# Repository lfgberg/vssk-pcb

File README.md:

# vssk-pcb
PCB for dudeship's VSSK keyboard

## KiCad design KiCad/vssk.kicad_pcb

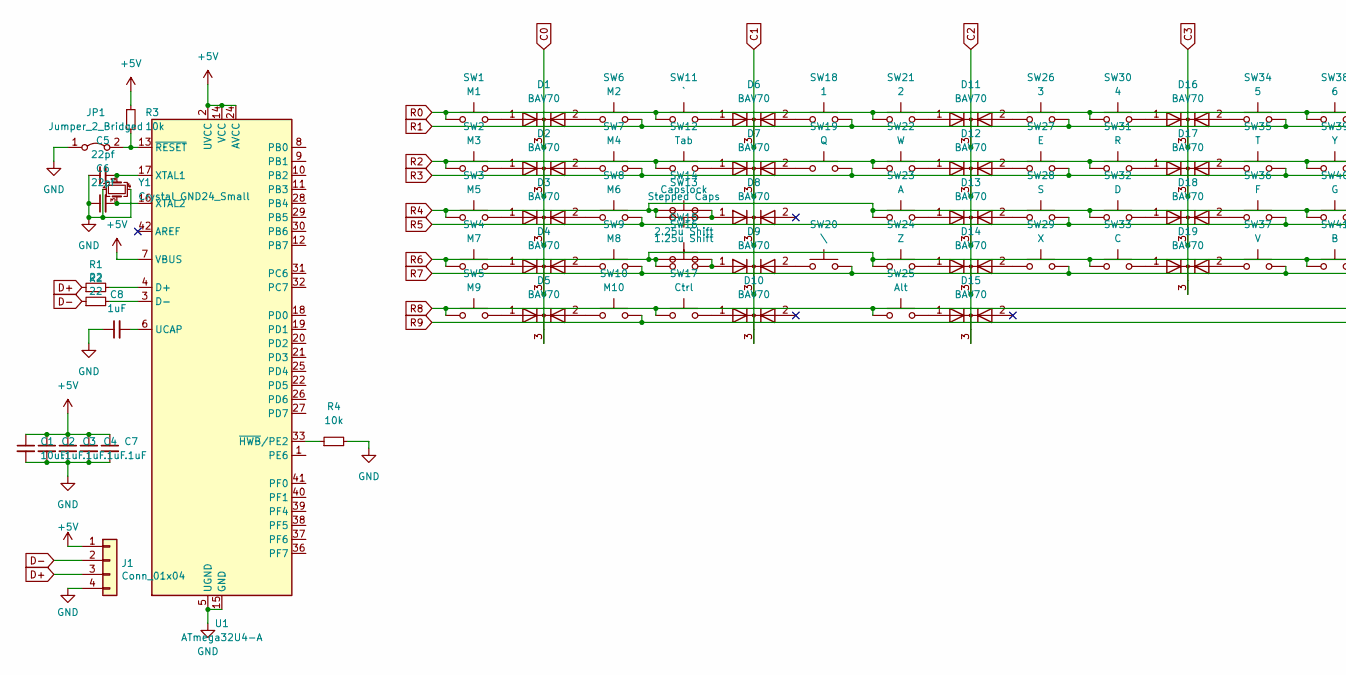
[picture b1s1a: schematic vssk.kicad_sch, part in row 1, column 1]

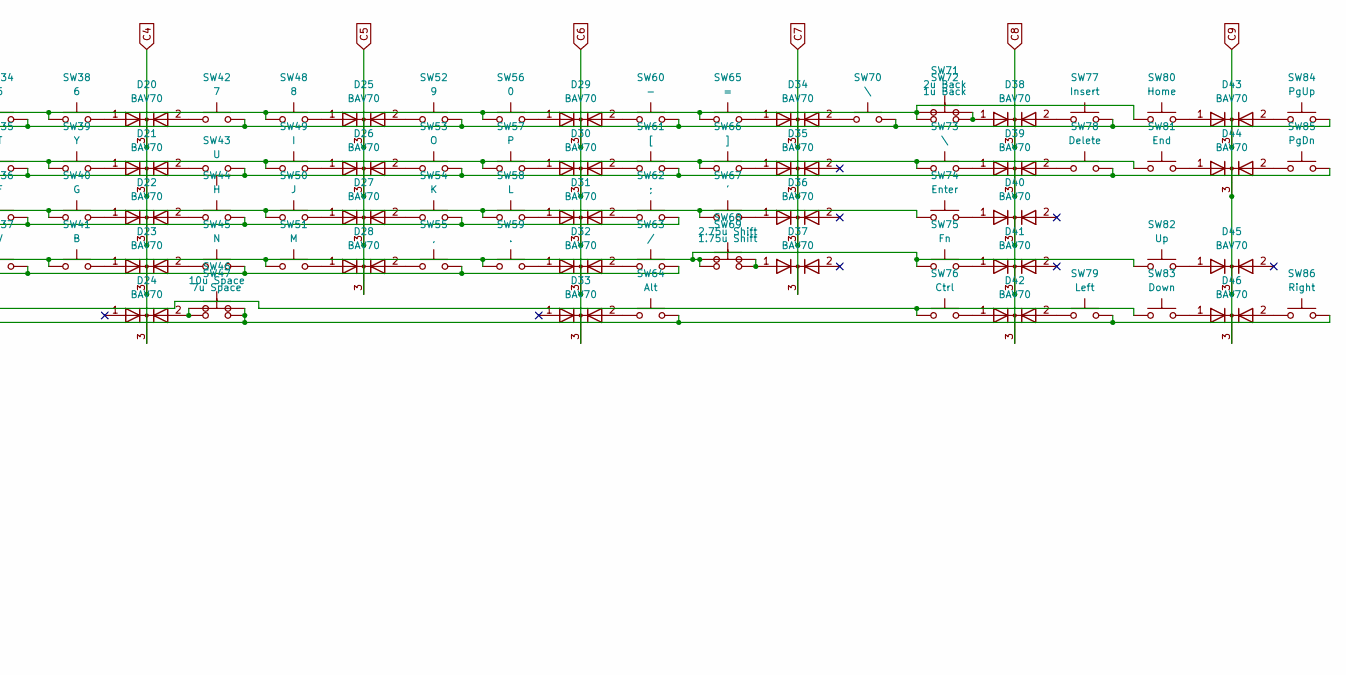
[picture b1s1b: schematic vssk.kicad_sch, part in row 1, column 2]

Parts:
C1: 10uF; C_0805_2012Metric
C2, C3, C4, C7: .1uF; C_0805_2012Metric
C5, C6: 22pf; C_0805_2012Metric
C8: 1uF; C_0805_2012Metric
D1, D2, D3, D4, D5, D6, D7, D8, D9, D10, D11, D12, D13, D14, D15, D16, D17, D18, D19, D20, D21, D22, D23, D24, D25, D26, D27, D28, D29, D30, D31, D32, D33, D34, D35, D36, D37, D38, D39, D40, D41, D42, D43, D44, D45, D46: BAV70; SOT-23
J1: Conn_01x04; JST-SR-4
JP1: Jumper_2_Bridged; ResetJumper
R1, R2: 22; R_0805_2012Metric
R3, R4: 10k; R_0805_2012Metric
SW1: M1; MX-1U-NoLED
SW2: M3; MX-1U-NoLED
SW3: M5; MX-1U-NoLED
SW4: M7; MX-1U-NoLED
SW5: M9; MX-1U-NoLED
SW6: M2; MX-1U-NoLED
SW7: M4; MX-1U-NoLED
SW8: M6; MX-1U-NoLED
SW9: M8; MX-1U-NoLED
SW10: M10; MX-1U-NoLED
SW11: `; MX-1U-NoLED
SW12: Tab; MX-1.5U-NoLED
SW13: Stepped Caps; MX-1.25U-NoLED
SW14: Capslock; MX-1.75U-NoLED
SW15: 2.25u Shift; MX-2.25U-NoLED
SW16: 1.25u Shift; MX-1.25U-NoLED
SW17, SW76: Ctrl; MX-1.5U-NoLED
SW18: 1; MX-1U-NoLED
SW19: Q; MX-1U-NoLED
SW20, SW70: \; MX-1U-NoLED
SW21: 2; MX-1U-NoLED
SW22: W; MX-1U-NoLED
SW23: A; MX-1U-NoLED
SW24: Z; MX-1U-NoLED
SW25, SW64: Alt; MX-1.5U-NoLED
SW26: 3; MX-1U-NoLED
SW27: E; MX-1U-NoLED
SW28: S; MX-1U-NoLED
SW29: X; MX-1U-NoLED
SW30: 4; MX-1U-NoLED
SW31: R; MX-1U-NoLED
SW32: D; MX-1U-NoLED
SW33: C; MX-1U-NoLED
SW34: 5; MX-1U-NoLED
SW35: T; MX-1U-NoLED
SW36: F; MX-1U-NoLED
SW37: V; MX-1U-NoLED
SW38: 6; MX-1U-NoLED
SW39: Y; MX-1U-NoLED
SW40: G; MX-1U-NoLED
SW41: B; MX-1U-NoLED
SW42: 7; MX-1U-NoLED
SW43: U; MX-1U-NoLED
SW44: H; MX-1U-NoLED
SW45: N; MX-1U-NoLED
SW46: 10u Space; MX-8U-ReversedStabilizers-NoLED
SW47: 7u Space; MX-7U-ReversedStabilizers-NoLED
SW48: 8; MX-1U-NoLED
SW49: I; MX-1U-NoLED
SW50: J; MX-1U-NoLED
SW51: M; MX-1U-NoLED
SW52: 9; MX-1U-NoLED
SW53: O; MX-1U-NoLED
SW54: K; MX-1U-NoLED
SW55: ,; MX-1U-NoLED
SW56: 0; MX-1U-NoLED
SW57: P; MX-1U-NoLED
SW58: L; MX-1U-NoLED
SW59: .; MX-1U-NoLED
SW60: -; MX-1U-NoLED
SW61: [; MX-1U-NoLED
SW62: ;; MX-1U-NoLED
SW63: /; MX-1U-NoLED
SW65: =; MX-1U-NoLED
SW66: ]; MX-1U-NoLED
SW67: '; MX-1U-NoLED
SW68: 2.75u Shift; MX-2.75U-NoLED
SW69: 1.75u Shift; MX-1.75U-NoLED
SW71: 2u Back; MX-2U-NoLED
SW72: 1u Back; MX-1U-NoLED
SW73: \; MX-1.5U-NoLED
SW74: Enter; MX-2.25U-NoLED
SW75: Fn; MX-1U-NoLED
SW77: Insert; MX-1U-NoLED
SW78: Delete; MX-1U-NoLED
SW79: Left; MX-1U-NoLED
SW80: Home; MX-1U-NoLED
SW81: End; MX-1U-NoLED
SW82: Up; MX-1U-NoLED
SW83: Down; MX-1U-NoLED
SW84: PgUp; MX-1U-NoLED
SW85: PgDn; MX-1U-NoLED
SW86: Right; MX-1U-NoLED
U1: ATmega32U4-A; QFN_TQFP-44_Combined
Y1: Crystal_GND24_Small; Crystal_SMD_3225-4Pin_3.2x2.5mm_HandSoldering

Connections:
+5V: C1.1, C2.1, C3.1, C4.1, C7.1, J1.1, R3.1, U1.2 (UVCC), U1.7 (VBUS), U1.14 (VCC), U1.24 (AVCC), U1.34 (VCC), U1.44 (AVCC)
C0: D1.3 (K), D2.3 (K), D3.3 (K), D4.3 (K), D5.3 (K)
C1: D6.3 (K), D7.3 (K), D8.3 (K), D9.3 (K), D10.3 (K)
C2: D11.3 (K), D12.3 (K), D13.3 (K), D14.3 (K), D15.3 (K)
C3: D16.3 (K), D17.3 (K), D18.3 (K), D19.3 (K)
C4: D20.3 (K), D21.3 (K), D22.3 (K), D23.3 (K), D24.3 (K)
C5: D25.3 (K), D26.3 (K), D27.3 (K), D28.3 (K)
C6: D29.3 (K), D30.3 (K), D31.3 (K), D32.3 (K), D33.3 (K)
C7: D34.3 (K), D35.3 (K), D36.3 (K), D37.3 (K)
C8: D38.3 (K), D39.3 (K), D40.3 (K), D41.3 (K), D42.3 (K)
C9: D43.3 (K), D44.3 (K), D45.3 (K), D46.3 (K)
D+: J1.3, R1.1
D-: J1.2, R2.1
GND: C1.2, C2.2, C3.2, C4.2, C5.1, C6.1, C7.2, C8.1, J1.4, JP1.1 (A), R4.2, U1.5 (UGND), U1.15 (GND), U1.23 (GND), U1.35 (GND), U1.43 (GND), Y1.2, Y1.4
unnamed: C5.2, U1.17 (XTAL1), Y1.1
unnamed: C6.2, U1.16 (XTAL2), Y1.3
unnamed: C8.2, U1.6 (UCAP)
unnamed: D1.1 (A), SW1.2
unnamed: D1.2 (A), SW6.1
unnamed: D2.1 (A), SW2.2
unnamed: D2.2 (A), SW7.1
unnamed: D3.1 (A), SW3.2
unnamed: D3.2 (A), SW8.1
unnamed: D4.1 (A), SW4.2
unnamed: D4.2 (A), SW9.1
unnamed: D5.1 (A), SW5.2
unnamed: D5.2 (A), SW10.1
unnamed: D6.1 (A), SW11.2
unnamed: D6.2 (A), SW18.1
unnamed: D7.1 (A), SW12.2
unnamed: D7.2 (A), SW19.1
unnamed: D8.1 (A), SW13.1, SW14.2
unnamed: D9.1 (A), SW15.2, SW16.2
unnamed: D9.2 (A), SW20.1
unnamed: D10.1 (A), SW17.2
unnamed: D11.1 (A), SW21.2
unnamed: D11.2 (A), SW26.1
unnamed: D12.1 (A), SW22.2
unnamed: D12.2 (A), SW27.1
unnamed: D13.1 (A), SW23.2
unnamed: D13.2 (A), SW28.1
unnamed: D14.1 (A), SW24.2
unnamed: D14.2 (A), SW29.1
unnamed: D15.1 (A), SW25.2
unnamed: D16.1 (A), SW30.2
unnamed: D16.2 (A), SW34.1
unnamed: D17.1 (A), SW31.2
unnamed: D17.2 (A), SW35.1
unnamed: D18.1 (A), SW32.2
unnamed: D18.2 (A), SW36.1
unnamed: D19.1 (A), SW33.2
unnamed: D19.2 (A), SW37.1
unnamed: D20.1 (A), SW38.2
unnamed: D20.2 (A), SW42.1
unnamed: D21.1 (A), SW39.2
unnamed: D21.2 (A), SW43.1
unnamed: D22.1 (A), SW40.2
unnamed: D22.2 (A), SW44.1
unnamed: D23.1 (A), SW41.2
unnamed: D23.2 (A), SW45.1
unnamed: D24.2 (A), SW46.1, SW47.1
unnamed: D25.1 (A), SW48.2
unnamed: D25.2 (A), SW52.1
unnamed: D26.1 (A), SW49.2
unnamed: D26.2 (A), SW53.1
unnamed: D27.1 (A), SW50.2
unnamed: D27.2 (A), SW54.1
unnamed: D28.1 (A), SW51.2
unnamed: D28.2 (A), SW55.1
unnamed: D29.1 (A), SW56.2
unnamed: D29.2 (A), SW60.1
unnamed: D30.1 (A), SW57.2
unnamed: D30.2 (A), SW61.1
unnamed: D31.1 (A), SW58.2
unnamed: D31.2 (A), SW62.1
unnamed: D32.1 (A), SW59.2
unnamed: D32.2 (A), SW63.1
unnamed: D33.2 (A), SW64.1
unnamed: D34.1 (A), SW65.2
unnamed: D34.2 (A), SW70.1
unnamed: D35.1 (A), SW66.2
unnamed: D36.1 (A), SW67.2
unnamed: D37.1 (A), SW68.2, SW69.2
unnamed: D38.1 (A), SW71.2, SW72.2
unnamed: D38.2 (A), SW77.1
unnamed: D39.1 (A), SW73.2
unnamed: D39.2 (A), SW78.1
unnamed: D40.1 (A), SW74.2
unnamed: D41.1 (A), SW75.2
unnamed: D42.1 (A), SW76.2
unnamed: D42.2 (A), SW79.1
unnamed: D43.1 (A), SW80.2
unnamed: D43.2 (A), SW84.1
unnamed: D44.1 (A), SW81.2
unnamed: D44.2 (A), SW85.1
unnamed: D45.1 (A), SW82.2
unnamed: D46.1 (A), SW83.2
unnamed: D46.2 (A), SW86.1
unnamed: JP1.2 (B), R3.2, U1.13 (~RESET)
unnamed: R1.2, U1.4 (D+)
unnamed: R2.2, U1.3 (D-)
unnamed: R4.1, U1.33 (~HWB/PE2)
R0: SW1.1, SW11.1, SW21.1, SW30.1, SW38.1, SW48.1, SW56.1, SW65.1, SW71.1, SW72.1, SW80.1
R1: SW6.2, SW18.2, SW26.2, SW34.2, SW42.2, SW52.2, SW60.2, SW70.2, SW77.2, SW84.2
R2: SW2.1, SW12.1, SW22.1, SW31.1, SW39.1, SW49.1, SW57.1, SW66.1, SW73.1, SW81.1
R3: SW7.2, SW19.2, SW27.2, SW35.2, SW43.2, SW53.2, SW61.2, SW78.2, SW85.2
R4: SW3.1, SW13.2, SW14.1, SW23.1, SW32.1, SW40.1, SW50.1, SW58.1, SW67.1, SW74.1
R5: SW8.2, SW28.2, SW36.2, SW44.2, SW54.2, SW62.2
R6: SW4.1, SW15.1, SW16.1, SW24.1, SW33.1, SW41.1, SW51.1, SW59.1, SW68.1, SW69.1, SW75.1, SW82.1
R7: SW9.2, SW20.2, SW29.2, SW37.2, SW45.2, SW55.2, SW63.2
R8: SW5.1, SW17.1, SW25.1, SW76.1, SW83.1
R9: SW10.2, SW46.2, SW47.2, SW64.2, SW79.2, SW86.2

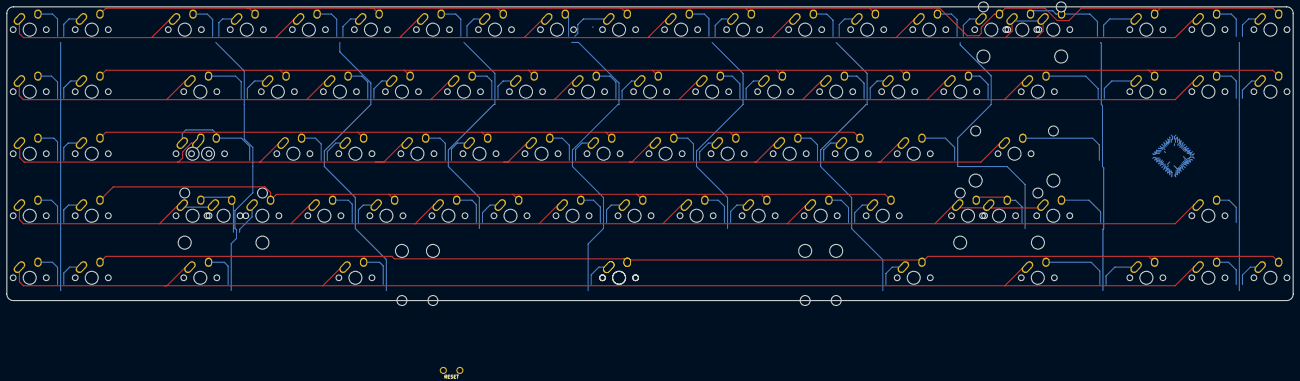
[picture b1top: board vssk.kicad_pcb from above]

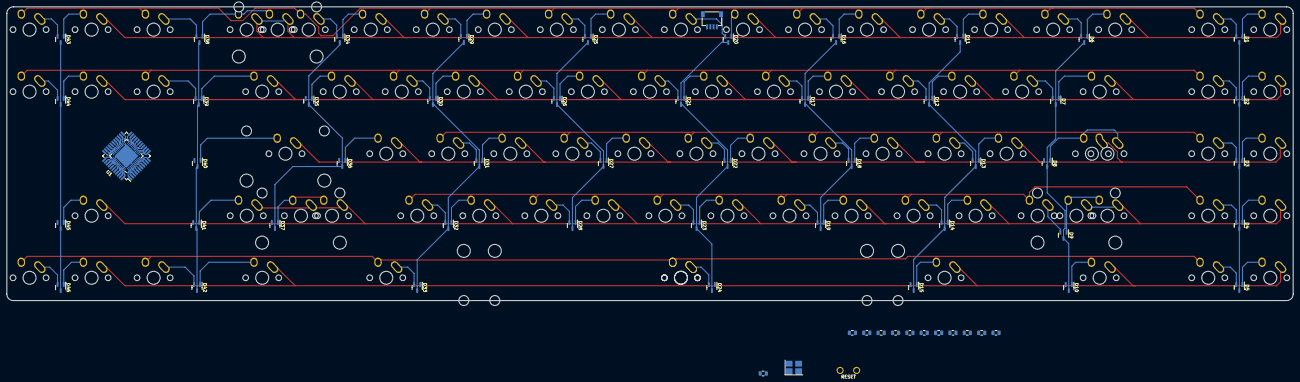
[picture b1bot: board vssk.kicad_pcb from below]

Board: 2 copper layers, 395.0 x 90.2 mm, 148 parts (61 on the bottom side), 112 nets.

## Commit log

2021-10-25 Finish Schematic, add Reference Files
2021-10-26 placed switch footprints
2021-10-27 placed/routed diodes
2021-10-28 routed rows/cols
2021-10-28 placed jst connector
